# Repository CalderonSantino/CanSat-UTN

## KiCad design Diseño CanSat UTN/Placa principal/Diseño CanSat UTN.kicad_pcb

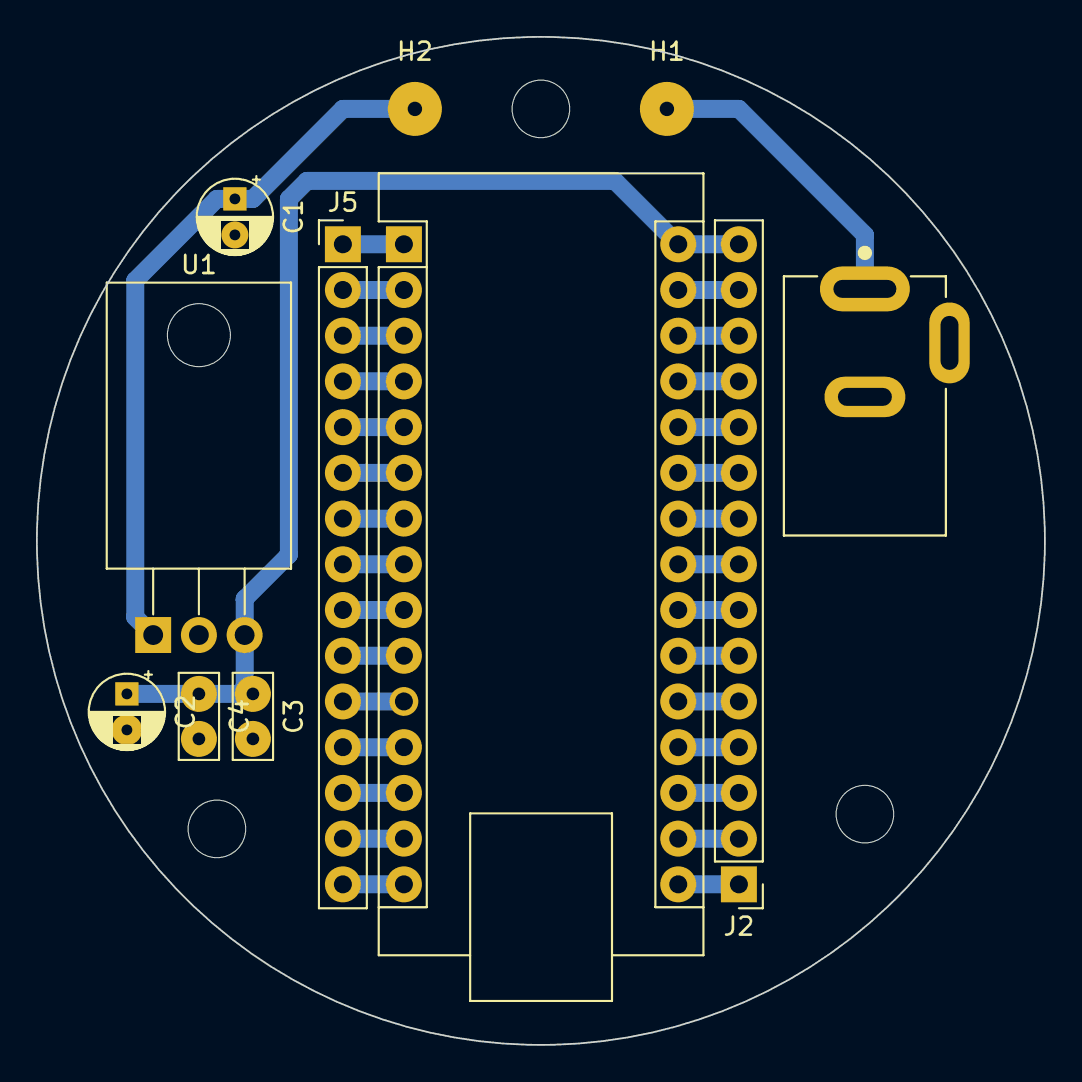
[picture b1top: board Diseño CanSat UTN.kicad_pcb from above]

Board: 2 copper layers, 56.0 x 56.0 mm, 11 parts (0 on the bottom side), 31 nets.

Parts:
A1: Arduino_Nano_v3.x; Arduino_Nano
C1, C2: C_Polarized; CP_Radial_D4.0mm_P2.00mm
C3, C4: C; C_Rect_L4.6mm_W2.0mm_P2.50mm_MKS02_FKP02
H1, H2: MountingHole_Pad; MountingHole_2.2mm_M2_Pad
J1: Jack-DC
J2, J5: Conn_01x15_MountingPin; PinHeader_1x15_P2.54mm_Vertical
U1: L7805; TO-220-3_Horizontal_TabDown

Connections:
+5V: A1.30 (VIN), C2.1, C3.1, C4.1, J2.15, U1.3 (OUT)
+9V: H1.2 (1), J1.1
/Arduino Nano/1: A1.1 (D1/TX), J5.1
/Arduino Nano/2: A1.2 (D0/RX), J5.2
/Arduino Nano/3: A1.3 (~RESET), J5.3
/Arduino Nano/5: A1.5 (D2), J5.5
/Arduino Nano/6: A1.6 (D3), J5.6
/Arduino Nano/7: A1.7 (D4), J5.7
/Arduino Nano/8: A1.8 (D5), J5.8
/Arduino Nano/9: A1.9 (D6), J5.9
/Arduino Nano/10: A1.10 (D7), J5.10
/Arduino Nano/11: A1.11 (D8), J5.11
/Arduino Nano/12: A1.12 (D9), J5.12
/Arduino Nano/13: A1.13 (D10), J5.13
/Arduino Nano/14: A1.14 (D11), J5.14
/Arduino Nano/15: A1.15 (D12), J5.15
/Arduino Nano/16: A1.16 (D13), J2.1
/Arduino Nano/17: A1.17 (3V3), J2.2
/Arduino Nano/18: A1.18 (AREF), J2.3
/Arduino Nano/19: A1.19 (A0), J2.4
/Arduino Nano/20: A1.20 (A1), J2.5
/Arduino Nano/21: A1.21 (A2), J2.6
/Arduino Nano/22: A1.22 (A3), J2.7
/Arduino Nano/23: A1.23 (A4), J2.8
/Arduino Nano/24: A1.24 (A5), J2.9
/Arduino Nano/25: A1.25 (A6), J2.10
/Arduino Nano/26: A1.26 (A7), J2.11
/Arduino Nano/27: A1.27 (+5V), J2.12
/Arduino Nano/28: A1.28 (~RESET), J2.13
GND: A1.4 (GND), A1.29 (GND), C1.2, C2.2, C3.2, C4.2, J1.2, J2.14, J5.4, U1.2 (GND)
unnamed: C1.1, H2.1, U1.1 (IN)

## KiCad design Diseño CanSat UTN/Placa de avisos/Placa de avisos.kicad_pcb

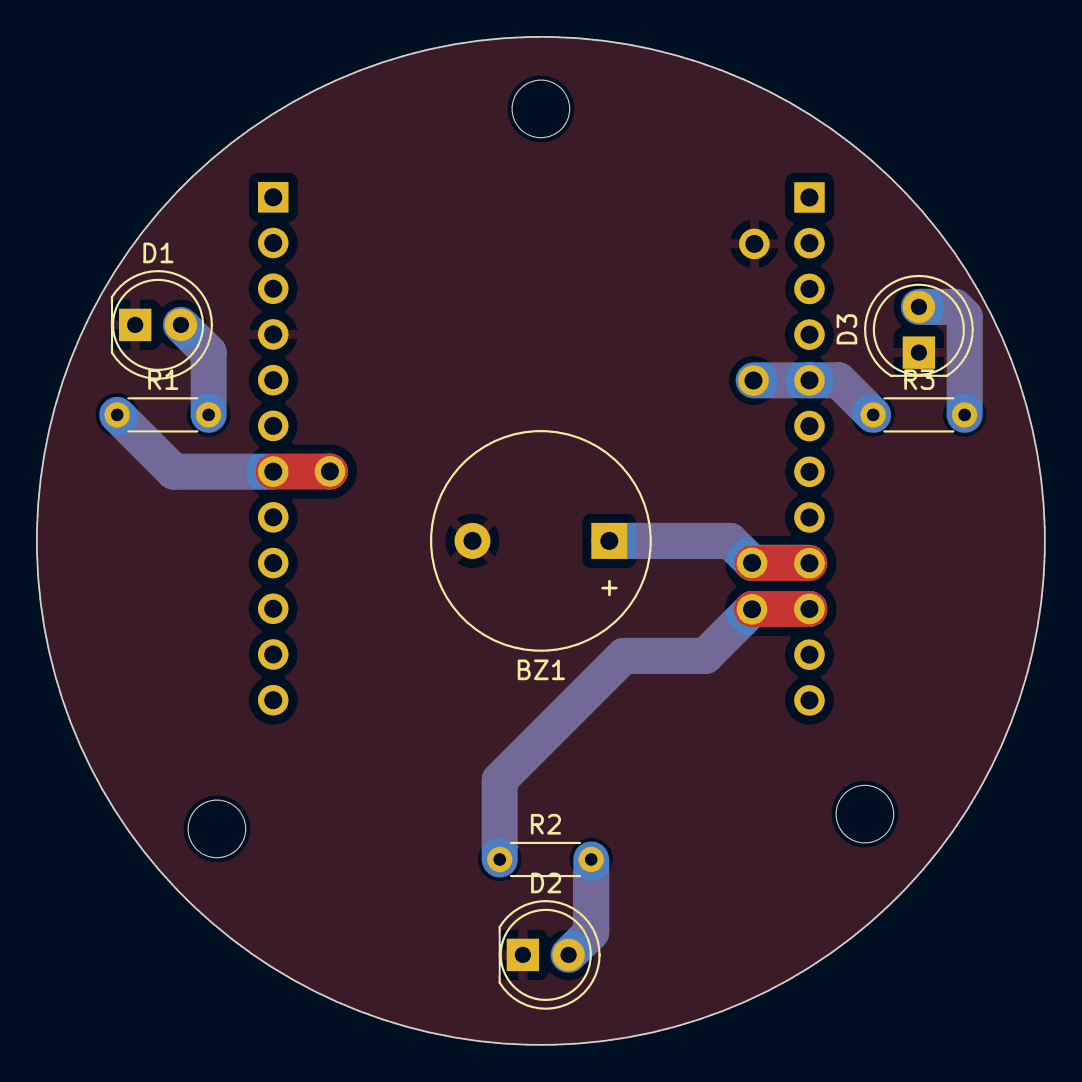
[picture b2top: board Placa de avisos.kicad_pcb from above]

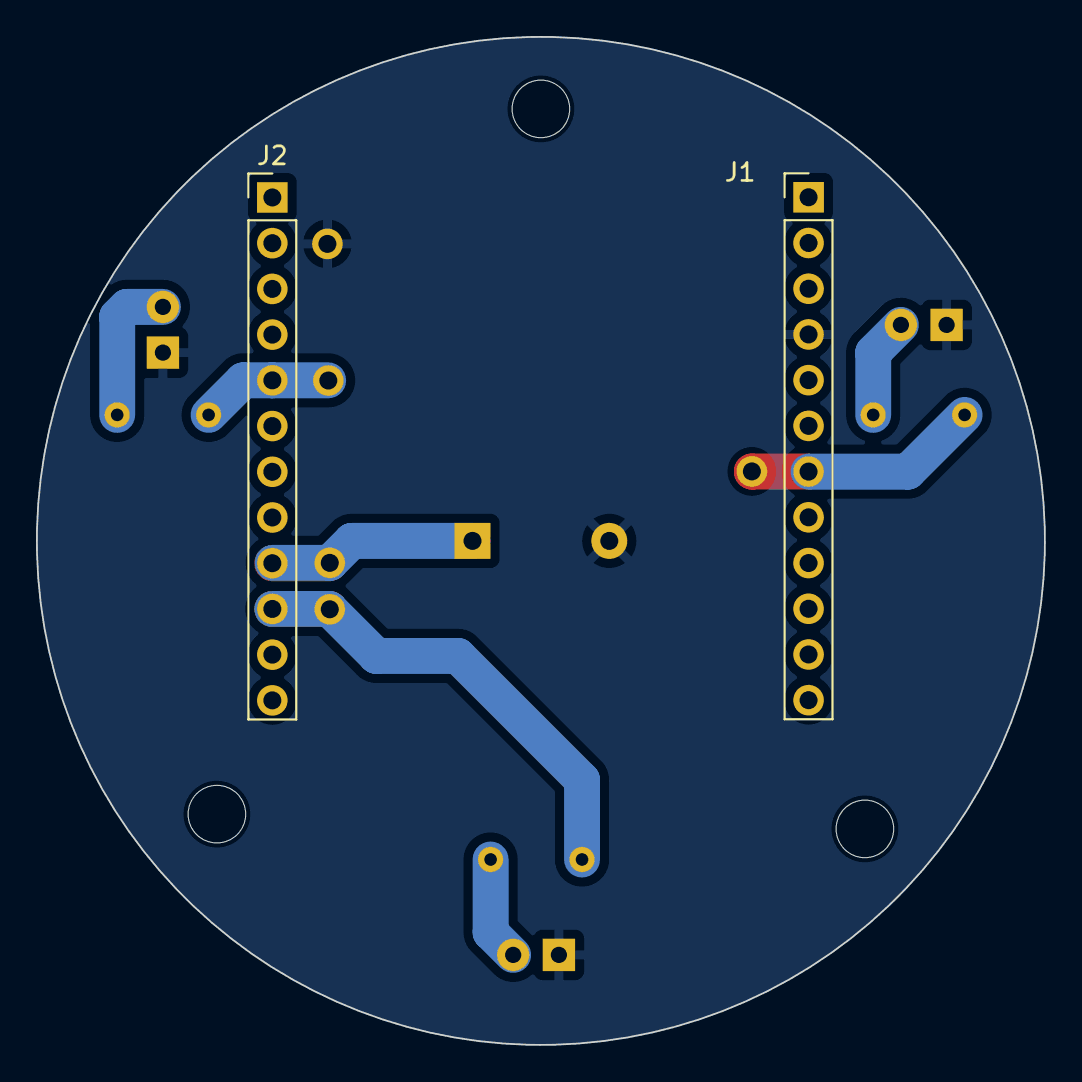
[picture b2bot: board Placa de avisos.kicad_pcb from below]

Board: 2 copper layers, 56.0 x 56.0 mm, 9 parts (2 on the bottom side), 8 nets.

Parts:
BZ1: Buzzer; Buzzer_12x9.5RM7.6
D1, D2, D3: LED; LED_D5.0mm
J1, J2: Conn_01x15_MountingPin; PinHeader_1x15_P2.54mm_Vertical
R1, R2, R3: R; R_Axial_DIN0204_L3.6mm_D1.6mm_P5.08mm_Horizontal

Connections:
/5: J2.5, R3.1
/9: BZ1.1 (-), J2.9
/10: J2.10, R2.1
/22: J1.7, R1.1
GND: BZ1.2 (+), D1.1 (K), D2.1 (K), D3.1 (K), J1.4
unnamed: D1.2 (A), R1.2
unnamed: D2.2 (A), R2.2
unnamed: D3.2 (A), R3.2

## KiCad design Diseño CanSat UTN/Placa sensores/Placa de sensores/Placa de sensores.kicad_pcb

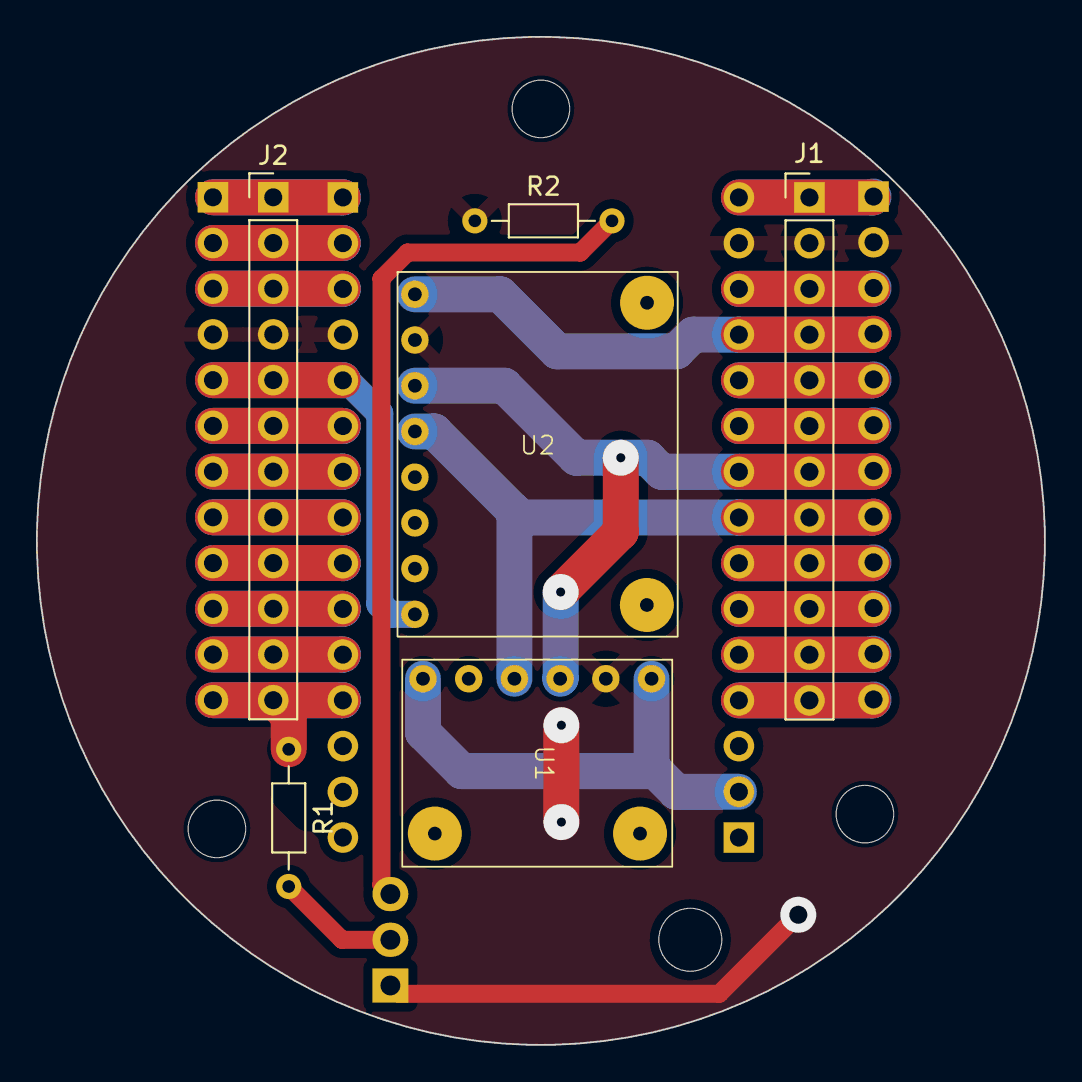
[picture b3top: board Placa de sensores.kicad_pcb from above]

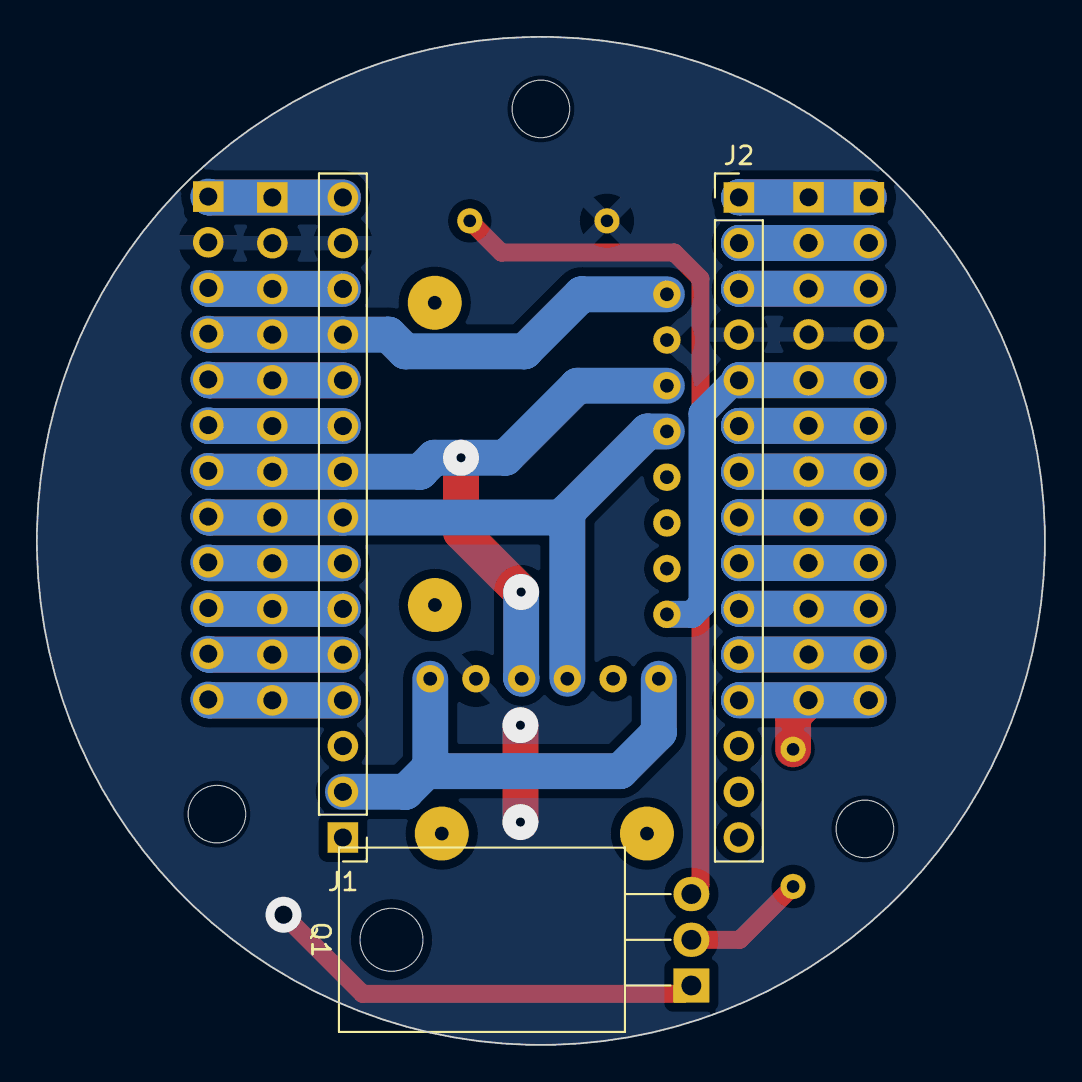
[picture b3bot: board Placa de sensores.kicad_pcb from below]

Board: 2 copper layers, 56.0 x 56.0 mm, 9 parts (3 on the bottom side), 25 nets.

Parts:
J1, J1#2, J2, J2#2: Conn_01x15_MountingPin; PinHeader_1x15_P2.54mm_Vertical
Q1: NPN; TO-220-3_Horizontal_TabDown
R1, R2: R; R_Axial_DIN0204_L3.6mm_D1.6mm_P7.62mm_Horizontal
U1: BMP280
U2: MPU6050

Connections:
/1: J2.1, J2#2.1
/2: J2.2, J2#2.2
/3: J2.3, J2#2.3
/5: J2.5, J2#2.5, U2.8 (INT)
/6: J2.6, J2#2.6
/7: J2.7, J2#2.7
/8: J2.8, J2#2.8
/9: J2.9, J2#2.9
/10: J2.10, J2#2.10
/11: J2.11, J2#2.11
/12: J2.12, J2#2.12, R1.1
/17: J1#2.2, U1.1 (VDD), U1.6 (SDO)
/19: J1.12, J1#2.4
/20: J1.11, J1#2.5
/21: J1.10, J1#2.6
/22: J1.9, J1#2.7
/23: J1.8, J1#2.8, U1.4 (SDI), U2.4 (SDA)
/24: J1.7, J1#2.9, U1.3 (SCK), U2.3 (SCL)
/25: J1.6, J1#2.10
/26: J1.5, J1#2.11
/28: J1.3, J1#2.13
/30: J1.1, J1#2.15
GND: J1.2, J1#2.14, J2.4, J2#2.4, R2.1, U1.2 (GND), U2.2 (GND)
unnamed: Q1.2 (B), R1.2
unnamed: J1.4, J1#2.12, Q1.3 (E), R2.2

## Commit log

2023-08-09 Subiendo codigo de prueba del sensor UV
2023-08-09 Subiendo recursos
2023-08-09 Actualizando recursos
2023-08-09 Subiendo test presion atm
2023-08-09 Subiendo librerias
2023-08-09 Subiendo test giroscopio
2023-08-09 Eliminando libreria
2023-08-10 Quitando librerias
2023-08-10 Subiendo circuitos
2023-08-10 Subiendo test sensores
2023-08-15 Subiendo diseño de CanSat; Placa Principal
2023-08-15 git ignore
2023-08-15 Eliminando Backups
2023-08-30 Subiendo Diseños
2023-09-27 Actualizando diseño
2023-09-28 actualizando diseños
2024-03-04 ACTUALIZACION
2024-03-04 Actualizando gitignore
2024-03-04 Eliminando
